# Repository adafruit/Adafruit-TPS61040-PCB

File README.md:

## Adafruit TPS61040 12V Bias Voltage Boost Converter PCB

<a href="http://www.adafruit.com/products/5644"><br/>
Click here to purchase one from the Adafruit shop</a>

PCB files for the Adafruit TPS61040 12V Bias Voltage Boost Converter. 

Format is EagleCAD schematic and board layout
* https://www.adafruit.com/product/5644

### Description

The Adafruit 12V Bias Voltage Boost Converter uses our new favorite mini-booster, the TI TPS61040, to generate a 12V DC from as little as 3V input. We use this chip a ton in our OLED boards, to generate the 12V bias voltage needed for the displays to function. But there's probably many other times and reasons you may want a high-ish voltage, such as driving an LED string backlight or re-programming FLASH or EEPROM memories.

Note that this board isn't good for high power driving, like solenoids or motors or long analog LED strips. You can get about 40mA out max. But definitely easier than getting a separate 12V supply when just a small amount of current is needed and you've already got 3.3 or 5V on the board.

You get one fully assembled breakout with a TPS61040 and required passive components, and a small bit of header. Give 2 to 6V DC on the IN and Ground pins. Then you'll have 12V on the 12V output pin. The Enable pin can be pulled low to disable the output.

### License

Adafruit invests time and resources providing this open source design, please support Adafruit and open-source hardware by purchasing products from [Adafruit](https://www.adafruit.com)!

Designed by Limor Fried/Ladyada for Adafruit Industries.

Creative Commons Attribution/Share-Alike, all text above must be included in any redistribution. 
See license.txt for additional details.

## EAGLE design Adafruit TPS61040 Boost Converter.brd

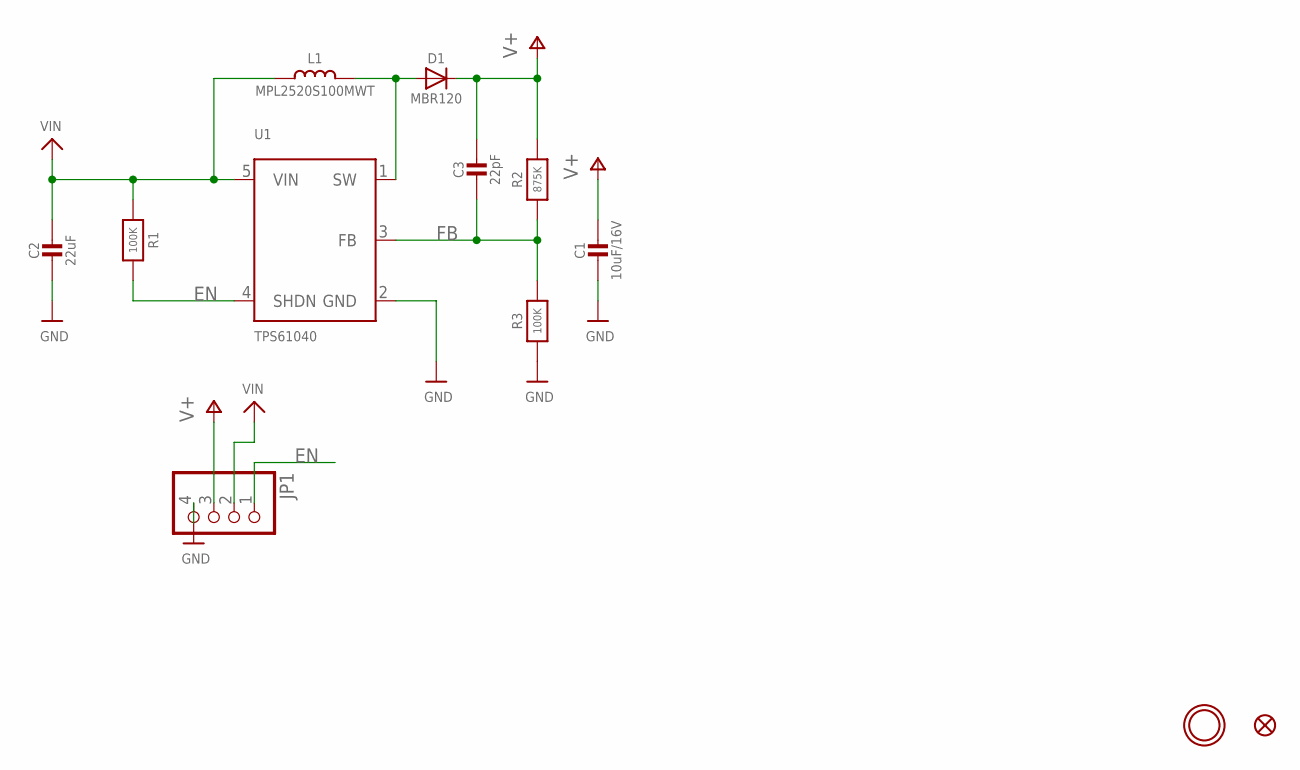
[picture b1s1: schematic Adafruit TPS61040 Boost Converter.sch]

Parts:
C1: 10uF/16V; 0805-NO
C2: 22uF; 0805-NO
C3: 22pF; 0603-NO
D1: MBR120; SOD-123FL
FID1: FIDUCIAL_1MM
JP1: HEADER-1X4ROUND; 1X04_ROUND
L1: MPL2520S100MWT; INDUCTOR_1007
R1, R3: 100K; 0603-NO
R2: 875K; 0603-NO
U1: TPS61040; SOT23-5
U$9: MOUNTINGHOLE2.5; MOUNTINGHOLE_2.5_PLATED

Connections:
EN: JP1.1, R1.2, U1.4 (SHDN)
FB: C3.2, R2.1, R3.2, U1.3 (FB)
GND: C1.2, C2.2, JP1.4, R3.1, U1.2 (GND)
unnamed: D1.A, L1.P$2 (2), U1.1 (SW)
V+: C1.1, C3.1, D1.C, JP1.3, R2.2
VIN: C2.1, JP1.2, L1.P$1 (1), R1.1, U1.5 (VIN)

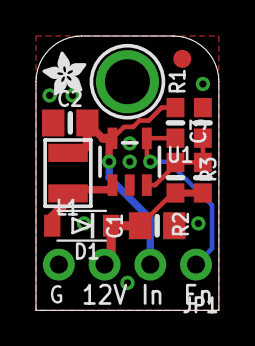
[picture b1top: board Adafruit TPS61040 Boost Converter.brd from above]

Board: 2 copper layers, 10.2 x 15.2 mm, 14 parts (1 on the bottom side), 6 nets.

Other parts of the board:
U$10: PCBFEAT-REV-040
U$11: ADAFRUIT_2.5MM

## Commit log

2024-01-09 cookiecutter

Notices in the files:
parts and their libraries:
microbuilder: This work is placed in the public domain, and may be freely used for commercial and non-commercial work with the following conditions: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
